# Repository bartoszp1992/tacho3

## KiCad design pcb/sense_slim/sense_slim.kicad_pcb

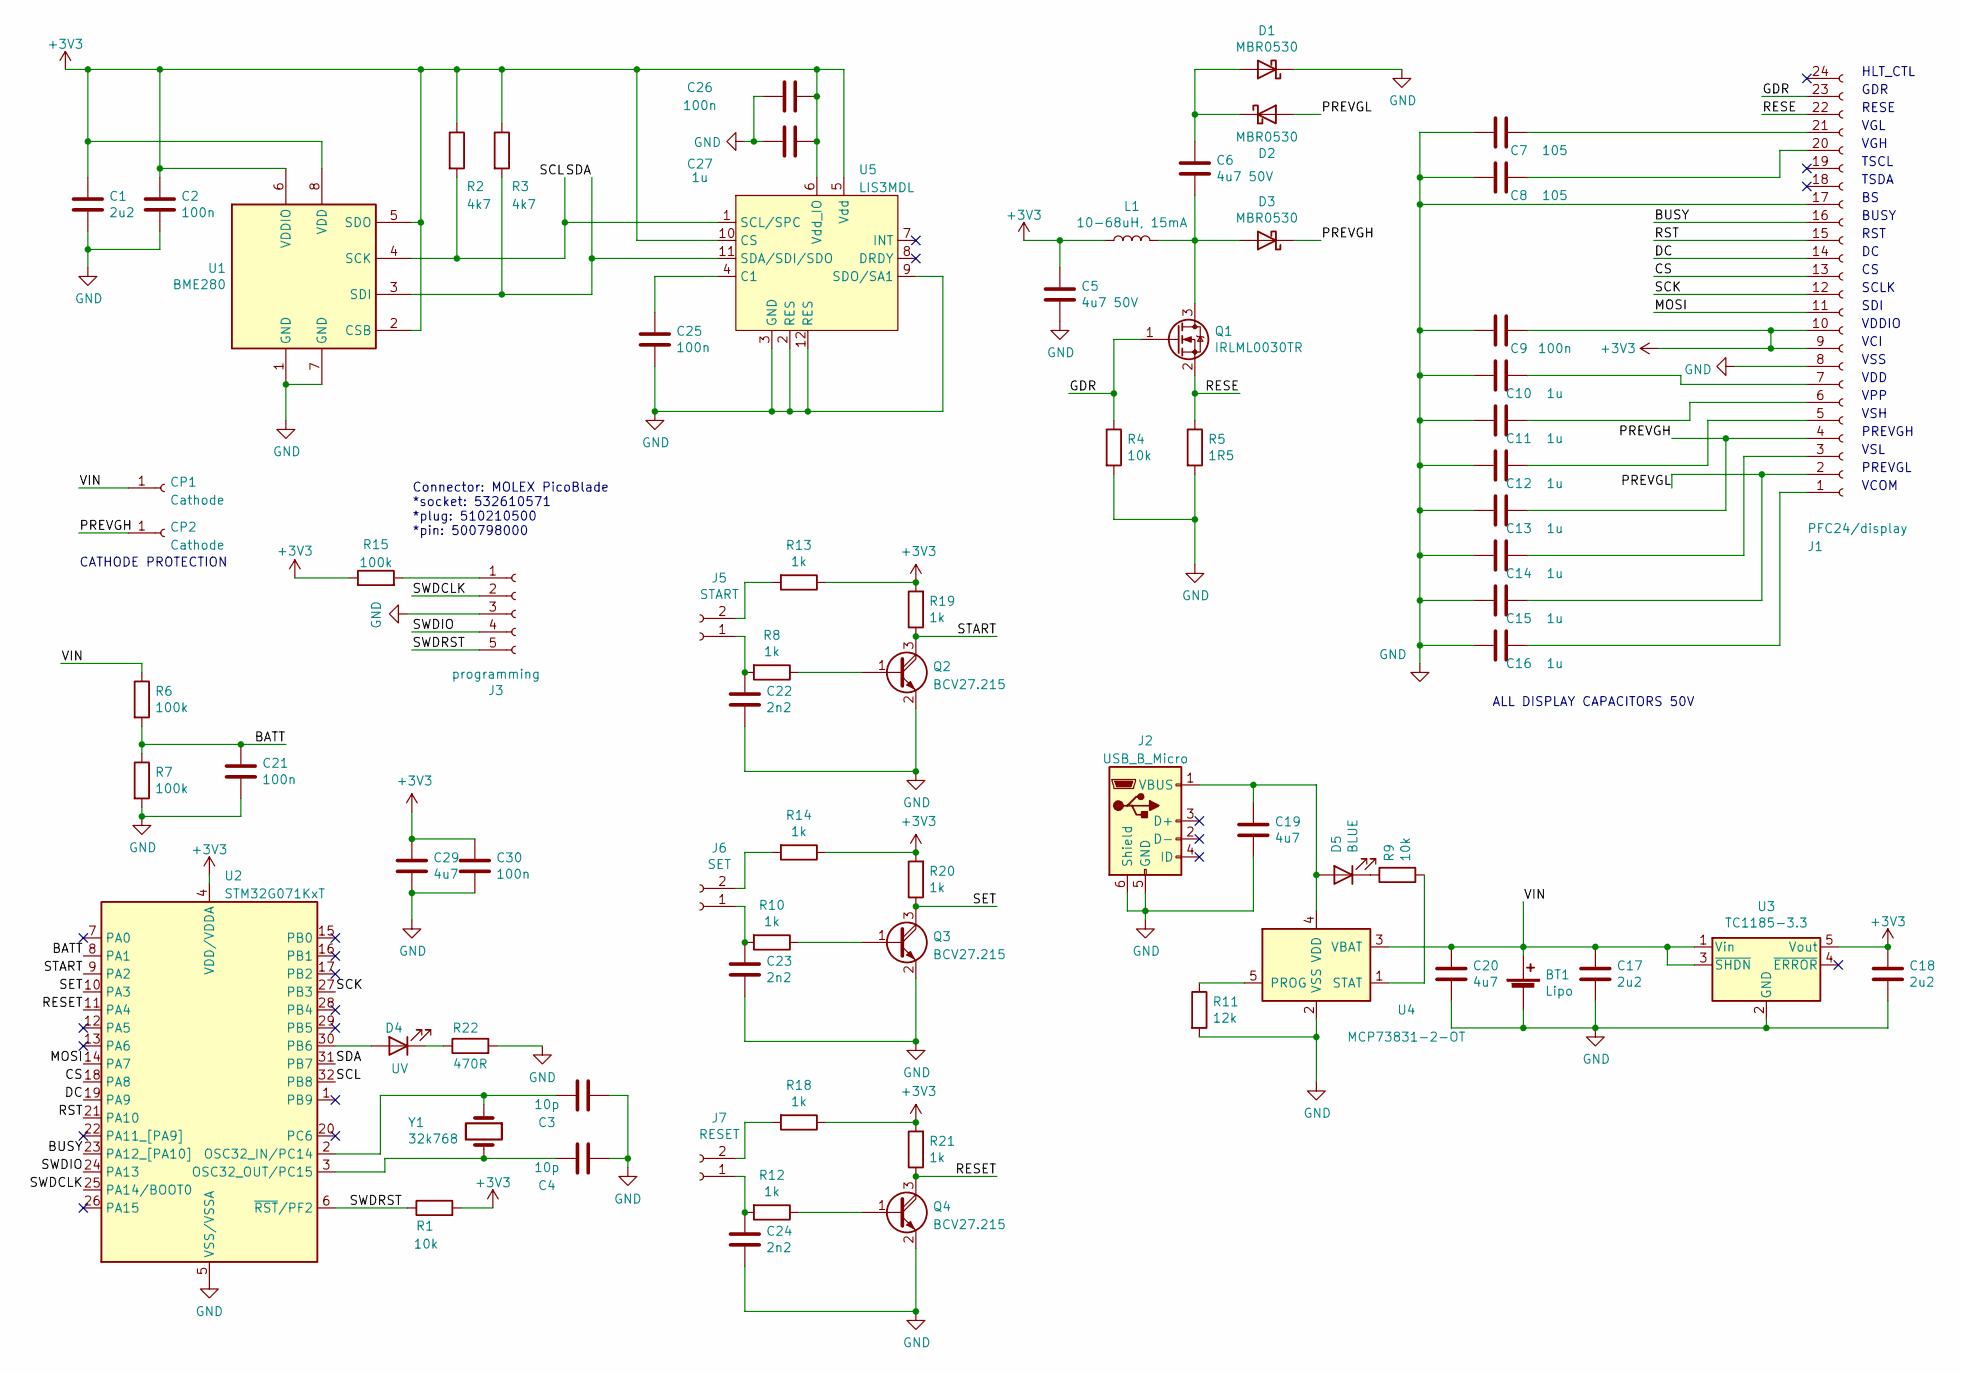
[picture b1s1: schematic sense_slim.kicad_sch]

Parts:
BT1: Lipo; R_2010_5025Metric
C1, C17, C18: 2u2; C_0603_1608Metric
C2, C9, C21, C25, C26, C30: 100n; C_0603_1608Metric
C3, C4: 10p; C_0603_1608Metric
C5, C6: 4u7 50V; C_0805_2012Metric
C7, C8: 105; C_0603_1608Metric
C10, C11, C12, C13, C14, C15, C16, C27: 1u; C_0603_1608Metric
C19, C20, C29: 4u7; C_0603_1608Metric
C22, C23, C24: 2n2; C_0603_1608Metric
CP1, CP2: Cathode; TestPoint_Pad_3.0x3.0mm
D1, D2, D3: MBR0530; D_SOD-123
D4: UV; LED_0603_1608Metric
D5: BLUE; D_0603_1608Metric
J1: PFC24/display; FPC-24P-P0.50mm_Universal
J2: USB_B_Micro; USB_Micro-B_Molex_47346-0001
J3: programming; DEGSON PicoBlade 5P SMD
J5: START; PinHeader_1x02_P2.54mm_Vertical
J6: SET; PinHeader_1x02_P2.54mm_Vertical
J7: RESET; PinHeader_1x02_P2.54mm_Vertical
L1: 10-68uH, 15mA; R_1206_3216Metric
Q1: IRLML0030TR; SOT-23
Q2, Q3, Q4: BCV27.215; SOT-23
R1, R4, R9: 10k; R_0603_1608Metric
R2, R3: 4k7; R_0603_1608Metric
R5: 1R5; R_0603_1608Metric
R6, R7, R15: 100k; R_0603_1608Metric
R8, R10, R12, R13, R14, R18, R19, R20, R21: 1k; R_0603_1608Metric
R11: 12k; R_0603_1608Metric
R22: 470R; R_0603_1608Metric
U1: BME280; Bosch_LGA-8_2.5x2.5mm_P0.65mm_ClockwisePinNumbering
U2: STM32G071KxT; LQFP-32_7x7mm_P0.8mm
U3: TC1185-3.3; SOT-23-5
U4: MCP73831-2-OT; SOT-23-5
U5: LIS3MDL; LGA-12_2x2mm_P0.5mm
Y1: 32k768; PinHeader_1x02_P2.00mm_Vertical

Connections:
+3V3: C1.1, C2.1, C5.1, C9.1, C18.1, C26.1, C27.1, C29.1, C30.1, J1.9, J1.10, L1.1, R1.2, R2.1, R3.1, R13.1, R14.1, R15.1, R18.1, R19.2, R20.2, R21.2, U1.2 (CSB), U1.5 (SDO), U1.6 (VDDIO), U1.8 (VDD), U2.4 (VDD/VDDA), U3.5 (Vout), U5.5 (Vdd), U5.6 (Vdd_IO), U5.10 (CS)
/BATT: C21.1, R6.2, R7.1, U2.8 (PA1)
/BUSY: J1.16, U2.23 (PA12_[PA10])
/CS: J1.13, U2.18 (PA8)
/DC: J1.14, U2.19 (PA9)
/GDR: J1.23, Q1.1 (G), R4.1
/MOSI: J1.11, U2.14 (PA7)
/PREVGH: C13.1, CP2.1, D3.1 (K), J1.4
/PREVGL: C15.1, D2.2 (A), J1.2
/RESE: J1.22, Q1.2 (S), R5.1
/RESET: Q4.3 (C), R21.1, U2.11 (PA4)
/RST: J1.15, U2.21 (PA10)
/SCK: J1.12, U2.27 (PB3)
/SCL: R2.2, U1.4 (SCK), U2.32 (PB8), U5.1 (SCL/SPC)
/SDA: R3.2, U1.3 (SDI), U2.31 (PB7), U5.11 (SDA/SDI/SDO)
/SET: Q3.3 (C), R20.1, U2.10 (PA3)
/START: Q2.3 (C), R19.1, U2.9 (PA2)
/SWDCLK: J3.2, U2.25 (PA14/BOOT0)
/SWDIO: J3.4, U2.24 (PA13)
/SWDRST: J3.5, R1.1, U2.6 (~RST/PF2)
/VIN: BT1.1 (+), C17.1, C20.1, CP1.1, R6.1, U3.1 (Vin), U3.3 (~SHDN), U4.3 (VBAT)
GND: BT1.2 (-), C1.2, C2.2, C3.2, C4.2, C5.2, C7.2, C8.2, C9.2, C10.2, C11.2, C12.2, C13.2, C14.2, C15.2, C16.2, C17.2, C18.2, C19.2, C20.2, C21.2, C22.2, C23.2, C24.2, C25.2, C26.2, C27.2, C29.2, C30.2, D1.1 (K), J1.8, J1.17, J2.5 (GND), J2.6 (Shield), J3.3, Q2.2 (E), Q3.2 (E), Q4.2 (E), R4.2, R5.2, R7.2, R11.2, R22.2, U1.1 (GND), U1.7 (GND), U2.5 (VSS/VSSA), U3.2 (GND), U4.2 (VSS), U5.2 (RES), U5.3 (GND), U5.9 (SDO/SA1), U5.12 (RES)
unnamed: C3.1, U2.2 (OSC32_IN/PC14), Y1.1
unnamed: C4.1, U2.3 (OSC32_OUT/PC15), Y1.2
unnamed: C6.1, D1.2 (A), D2.1 (K)
unnamed: C6.2, D3.2 (A), L1.2, Q1.3 (D)
unnamed: C7.1, J1.21
unnamed: C8.1, J1.20
unnamed: C10.1, J1.7
unnamed: C11.1, J1.6
unnamed: C12.1, J1.5
unnamed: C14.1, J1.3
unnamed: C16.1, J1.1
unnamed: C19.1, D5.2 (A), J2.1 (VBUS), U4.4 (VDD)
unnamed: C22.1, J5.1, R8.2
unnamed: C23.1, J6.1, R10.2
unnamed: C24.1, J7.1, R12.2
unnamed: C25.1, U5.4 (C1)
unnamed: D4.1 (K), R22.1
unnamed: D4.2 (A), U2.30 (PB6)
unnamed: D5.1 (K), R9.1
unnamed: J3.1, R15.2
unnamed: J5.2, R13.2
unnamed: J6.2, R14.2
unnamed: J7.2, R18.2
unnamed: Q2.1 (B), R8.1
unnamed: Q3.1 (B), R10.1
unnamed: Q4.1 (B), R12.1
unnamed: R9.2, U4.1 (STAT)
unnamed: R11.1, U4.5 (PROG)

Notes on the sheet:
VGH
PREVGH
GDR
TSCL
VDDIO
PREVGL
VGL
BUSY
VSL
VSS
Connector: MOLEX PicoBlade *socket: 532610571 *plug: 510210500 *pin: 500798000
SCLK
VSH
VCOM
CATHODE PROTECTION
VDD
ALL DISPLAY CAPACITORS 50V
TSDA
RST
VPP
HLT_CTL
VCI
RESE
SDI

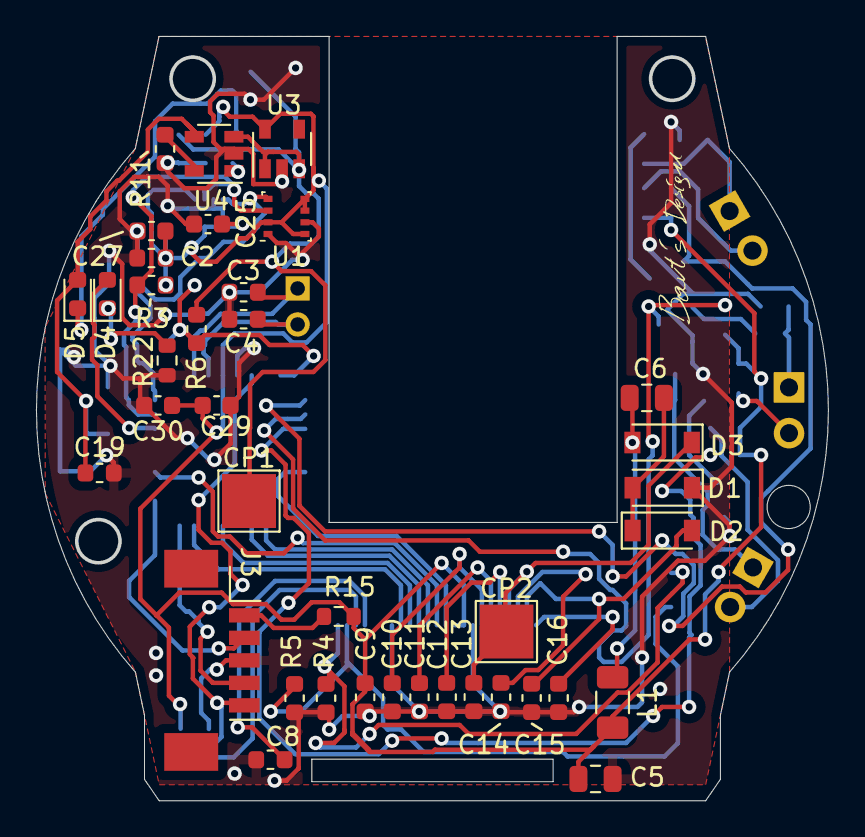
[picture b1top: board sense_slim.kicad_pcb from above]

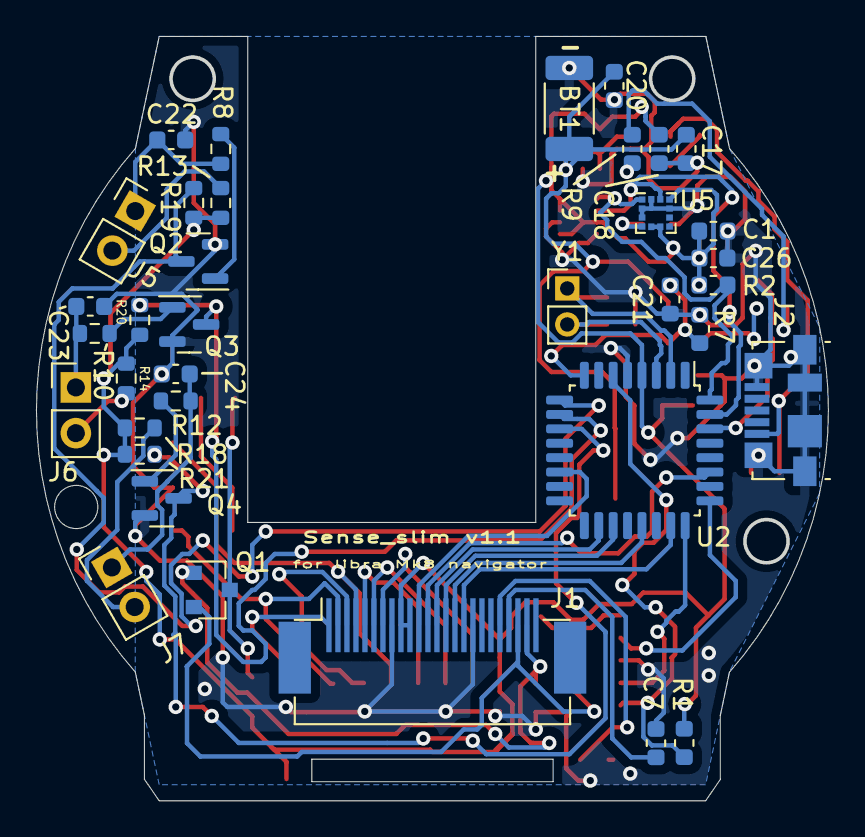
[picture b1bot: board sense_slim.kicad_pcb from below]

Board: 2 copper layers, 44.0 x 42.5 mm, 74 parts (36 on the bottom side), 50 nets.

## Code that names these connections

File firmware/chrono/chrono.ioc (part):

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Mcu.Name=STM32G071K(6-8-B)Tx
Mcu.Package=LQFP32
Mcu.UserName=STM32G071KBTx
PA1.GPIOParameters=GPIO_Label
PA1.GPIO_Label=BATT
PA1.Mode=IN1
PA1.Signal=ADC1_IN1
PA10.GPIOParameters=GPIO_Label
PA10.GPIO_Label=RST
PA10.Signal=GPIO_Output
PA12\ [PA10].GPIOParameters=GPIO_Label
PA12\ [PA10].GPIO_Label=BUSY
PA12\ [PA10].Signal=GPIO_Input
PA13.Mode=Serial_Wire
PA13.Signal=SYS_SWDIO
PA14-BOOT0.Mode=Serial_Wire
PA14-BOOT0.Signal=SYS_SWCLK
PA2.GPIOParameters=GPIO_PuPd,GPIO_Label,GPIO_ModeDefaultEXTI
PA2.GPIO_Label=BUTTON_START
PA2.GPIO_ModeDefaultEXTI=GPIO_MODE_IT_FALLING
PA2.GPIO_PuPd=GPIO_NOPULL
PA2.Signal=GPXTI2
PA3.GPIOParameters=GPIO_PuPd,GPIO_Label,GPIO_ModeDefaultEXTI
PA3.GPIO_Label=BUTTON_SET
PA3.GPIO_ModeDefaultEXTI=GPIO_MODE_IT_FALLING
PA3.GPIO_PuPd=GPIO_NOPULL
PA3.Signal=GPXTI3
PA4.GPIOParameters=GPIO_PuPd,GPIO_Label,GPIO_ModeDefaultEXTI
PA4.GPIO_Label=BUTTON_RESET
PA4.GPIO_ModeDefaultEXTI=GPIO_MODE_IT_FALLING
PA4.GPIO_PuPd=GPIO_NOPULL
PA4.Signal=GPXTI4
PA7.Mode=TX_Only_Simplex_Unidirect_Master
PA7.Signal=SPI1_MOSI
PA8.GPIOParameters=GPIO_Label
PA8.GPIO_Label=SPI_CS
PA8.Signal=GPIO_Output
PA9.GPIOParameters=GPIO_Label
PA9.GPIO_Label=DC
PA9.Signal=GPIO_Output
PB3.Mode=TX_Only_Simplex_Unidirect_Master
PB3.Signal=SPI1_SCK
PB6.GPIOParameters=GPIO_Label
PB6.GPIO_Label=LED_WKUP
PB6.Signal=GPIO_Output
PB7.Mode=I2C
PB7.Signal=I2C1_SDA
PB8.Mode=I2C
PB8.Signal=I2C1_SCL
PC14-OSC32_IN\ (PC14).Mode=LSE-External-Oscillator
PC14-OSC32_IN\ (PC14).Signal=RCC_OSC32_IN
PC15-OSC32_OUT\ (PC15).Mode=LSE-External-Oscillator
PC15-OSC32_OUT\ (PC15).Signal=RCC_OSC32_OUT
RCC.HSE_VALUE=8000000
RCC.SYSCLKFreq_VALUE=64000000
RCC.SYSCLKSource=RCC_SYSCLKSOURCE_PLLCLK
board=custom

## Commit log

2022-11-28 initial release
2022-11-28 almost working
2022-11-28 deleted debug filling forecast table
2022-11-29 added forecast icons
2022-11-29 dont sleep bug fixed
2022-11-29 fixed dont sleep bug
2022-11-30 fixed indexes, better forecast
2022-12-04 tacho scale added
2022-12-05 new base and ring
2022-12-07 working on SR version of ring
2022-12-08 working on new ring
2022-12-09 new ring
2022-12-11 small corrections
2022-12-12 corrected ring
2022-12-12 added SR manual
2022-12-12 no multiple definitions error
2022-12-13 3d case
2022-12-13 designing case
2022-12-13 renamed folder with 3D case version
2022-12-14 working on case
2022-12-15 new case prototype
2022-12-15 corrected case
2022-12-16 v0.2 case
2022-12-17 v0.3 case
2022-12-19 new case, wider placed dials
2022-12-19 version with case renamed to Mk2
2022-12-22 dd strap lock
2022-12-22 fixed dd lock
2022-12-24 lower case profile
2022-12-27 bigger fix posts holes
2022-12-28 case face reinforcement
2022-12-28 added LED cut in case
2022-12-29 fixed holders size
2022-12-30 generated output
2022-12-31 fixed symbols
2022-12-31 schemaric without ERC errors
2023-01-04 added license
2023-01-23 fixed start chrono bug
2023-03-17 added latch to case
2023-04-06 case on 2 bolts
2023-11-02 control commit
2025-09-30 dont remember
